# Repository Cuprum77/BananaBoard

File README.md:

# BananaBoard
## Project description
The BananaBoard is a solution to a problem of hooking up power supplies with standard 4mm Banana Plugs to Breadboards.
It was based on the idea of not having to own multiple cables and being easier to use, rather than relying on 4mm Banana Plug to Alligator clips or the 4mm Banana Plug to 2.54mm Pin header cables.

![alt text][trio]

## Design 
The PCB itself is designed around the [Keystone Electronics 575-4](https://www.keyelco.com/product.cfm/product_id/2379) Banana Plug sockets.

The design itself had to follow these requirements:
* Fit into the [BB830] breadboard popularized by [Ben Eater](https://eater.net/)
* Have footprints for at least 2 bypass capacitors per rail
* Onboard PTC fuse to avoid damage to the breadboard
* Bypass for PTC fuse if fuse is not desired
* Adjustable pin header slots so you can adjust it to your breadboard

So far all those requirements have been implemented on the first prototype.

## Breadboard Requirements
It *should* fit any board that fits within this dimension: 

  If the positive and negative rail are not mirrored on either side:
  * Positive rail to positive rail: 1.65" ± 0.025".

  If the positive rail and negative rail are mirrored on either side:
  * Positive rail to positive rail: 1.75" ± 0.025".

However, this has not been tested on any other breadboard than the [BB830]

![alt text][breadboard]

## Difficulties
Originally the project had no thermal relief under the idea that we should be limiting the current as little as possible, however that turned out to be a huge mistake as it made soldering almost impossible with a lower wattage iron due to the amount of copper. 
The uploaded version should be fixed and that should not be an issue with future orders.

## Art
To make the circuit board a bit more interesting, the users of the [Styropyro](https://styropyro.com/) Discord server was petitioned to come up with ideas on what to populate it with,
and does therefor contain artwork based off inside jokes and meme culture.

![alt text][singular]

## Connection
The design itself has connection indicators on the bottom side if one does not care for the artwork.
Example on suggested polarity
![alt text][pinout]
**Important**, the PCB itself is not polarized, does not have polarized components and does __not__ care if you connect it backwards!
However that assumes that you use non-polarized capacitors!

## Ordering
The files were sent off to to a manufacturer and got the ENIG treatment to enhance the artwork.
Total cost for the PCB came to aproximately €16.10 including shipping for 3 boards.

## Design files
If you desire to order these yourself, you can download the attached [gerber file](production/gerber.zip).
However you are encouraged to download the entire repo and verify the files yourself using
`git clone https://github.com/Cuprum77/BananaBoard.git`

Note that this project was originally built using KiCAD 6, however it has been updated to [KiCAD 7](https://www.kicad.org/download/).

## License
Hardware is licensed under [CERN OHL](LICENSE) while each artwork on the PCB are protected under their creators copyright and should be respected.

[singular]: https://github.com/Cuprum77/BananaBoard/blob/main/Images/single_pcb.jpg "PCBs from Aisler"
[trio]: https://github.com/Cuprum77/BananaBoard/blob/main/Images/all_pcbs.png "PCBs from Aisler"
[breadboard]: https://github.com/Cuprum77/BananaBoard/blob/main/Images/breadboard_example.jpg "PCBs from Aisler"
[pinout]: https://github.com/Cuprum77/BananaBoard/blob/main/Images/example-pinout.png "Pinout"
[BB830]: http://www.busboard.com/BB830T

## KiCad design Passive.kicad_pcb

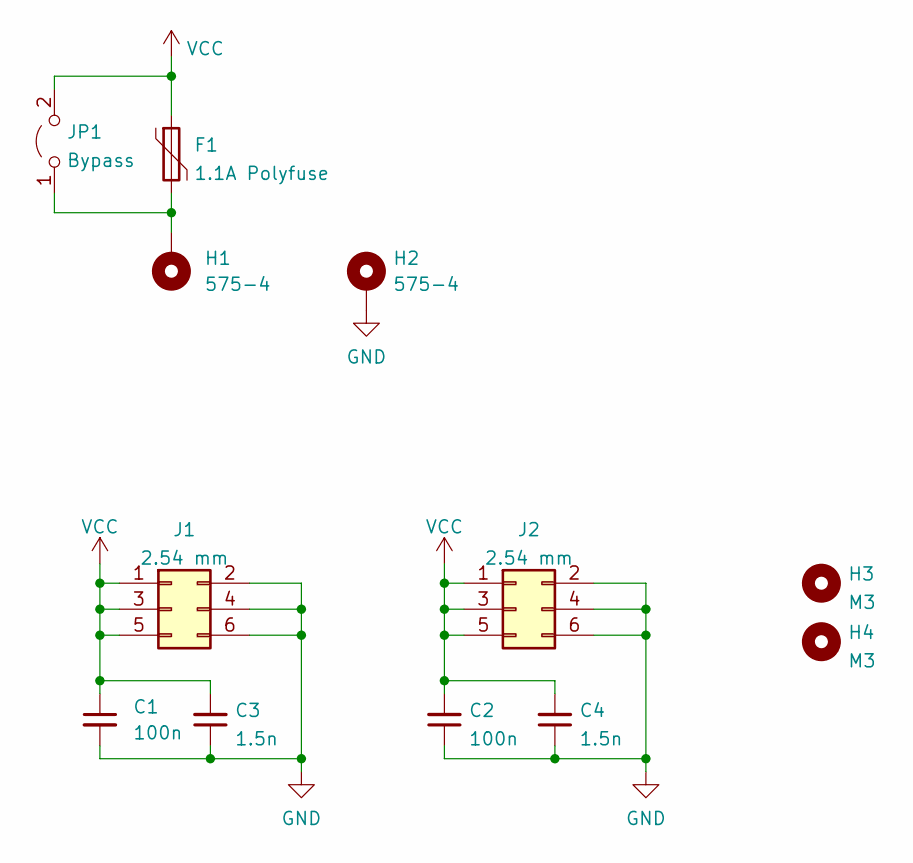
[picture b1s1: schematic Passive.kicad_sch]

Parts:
C1, C2: 100n; C_0603_1608Metric
C3, C4: 1.5n; C_0603_1608Metric
F1: 1.1A Polyfuse; Fuse_2920_7451Metric
H1, H2: 575-4; MountingHole_5.3mm_M5_DIN965_Pad_TopBottom
H3, H4: M3; MountingHole_3.2mm_M3_DIN965
J1, J2: 2.54 mm; PinHeader_2x03_P2.54mm_Vertical
JP1: Bypass; SolderJumper-2_P1.3mm_Open_Pad1.0x1.5mm

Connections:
GND: C1.2, C2.1, C3.1, C4.1, H2.1, J1.2, J1.4, J1.6, J2.2, J2.4, J2.6
unnamed: F1.2, H1.1, JP1.1 (A)
VCC: C1.1, C2.2, C3.2, C4.2, F1.1, J1.1, J1.3, J1.5, J2.1, J2.3, J2.5, JP1.2 (B)

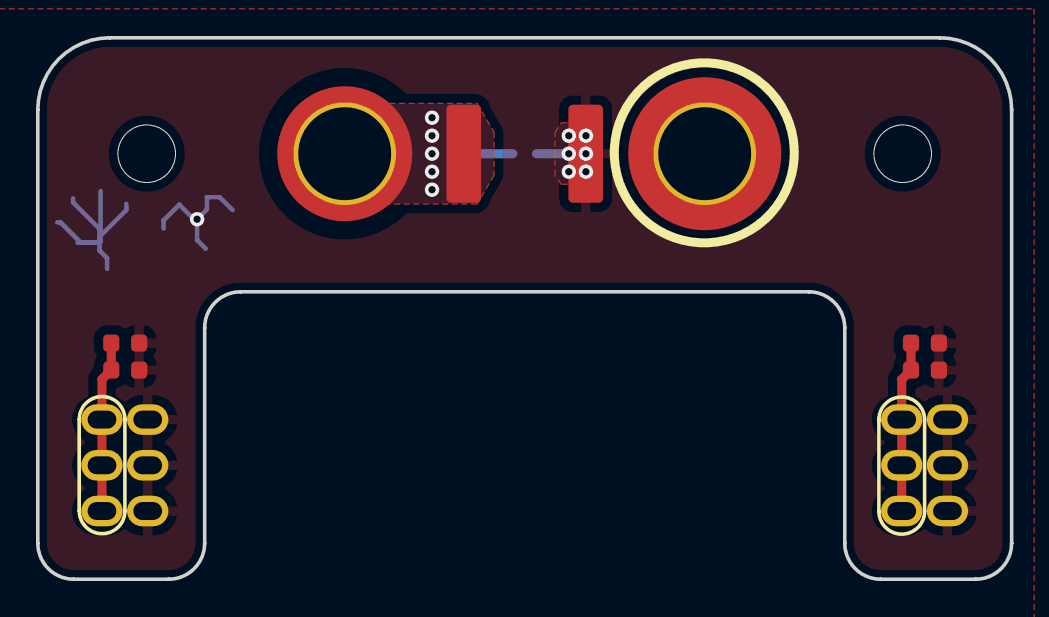
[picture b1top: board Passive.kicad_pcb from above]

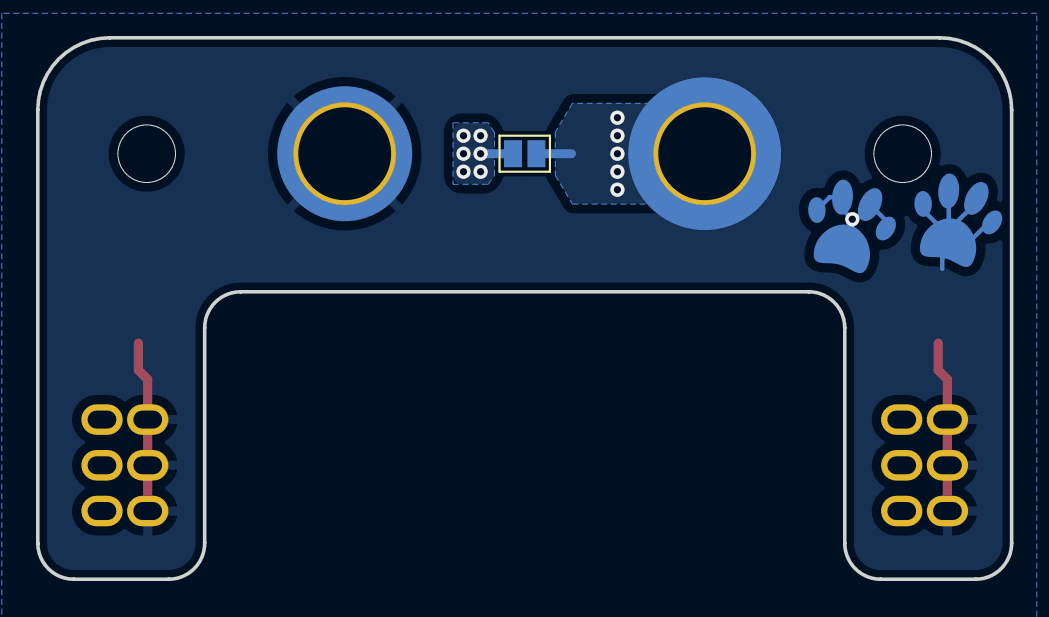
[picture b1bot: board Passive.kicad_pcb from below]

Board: 2 copper layers, 54.1 x 30.1 mm, 12 parts (4 on the bottom side), 3 nets.

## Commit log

2023-02-15 experimenting with readme
2023-02-15 Delete Passive-backups directory
    forgot to add to .gitignore
2023-02-16 readme change
2023-02-16 fixed extension typo
2023-02-16 fixed a couple typos and improved readme
2023-03-06 bom update
2024-01-09 remove ibom from linguist
